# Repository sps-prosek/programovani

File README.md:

# Programování – 3. ročník (Mechatronika)

Podklady pro předmět **Programování** na SPŠ, elektrotechnické zaměření – obor Mechatronika
(26-41-M/01 Elektrotechnika, ŠVP Mechatronika, platnost od 1. 9. 2024).
Ve 3. ročníku se navazuje na základy jazyka C z 2. ročníku a programuje se mikrokontroler
na platformě **Arduino** (ATmega328P – UNO / Nano).

**Dotace podle ŠVP:** 2 h týdně, 64 h v ročníku. Plán počítá s **50 h náplně
(25 dvouhodinovek)**, zbytek je rezerva na odpadlé hodiny, testy a dokončení projektů.

## Kde co je

| Cesta | Obsah |
|---|---|
| `plan/` | ŠVP (`6_SVP_M_2024.pdf`), tematický plán, přehled vybavení, mapování starých podkladů na nová témata. |
| `temata/` | Vlastní učivo. Jedna složka = jeden tematický blok, uvnitř prezentace, hodiny, úlohy, kód, obrázky a Moodle. |
| `temata/00_sablony/` | Šablony: prezentace (Beamer), příprava na hodinu, zadání úlohy, podklady pro Moodle. |
| `spolecne/` | Věci sdílené napříč tématy – Beamer motiv SPŠ a preambule, loga školy, společné obrázky, ukázky kódu. |
| `nastroje/` | Pomocné skripty: založení struktury, nové téma, překlad prezentací, přesun archivu. |
| `_archiv/` | Staré podklady z předchozích let (`3EA/`, `vyuka/`). Zdroj, ze kterého se materiál postupně přenáší do `temata/`. |

## Tematické bloky

| # | Téma | Hodin |
|---|---|---:|
| 01 | HW platformy a vývojové prostředí | 4 |
| 02 | Digitální výstupy – LED a bzučák | 2 |
| 03 | Digitální vstupy – tlačítka, pull-up, zákmity | 4 |
| 04 | Časování bez `delay()` – `millis()` a časovače | 4 |
| 05 | Stavové automaty – cyklistická blikačka | 4 |
| 06 | Funkce a strukturování kódu | 2 |
| 07 | Analogové vstupy a PWM | 4 |
| 08 | Sériová linka (UART) | 2 |
| 09 | Pole a řetězce – parsování příkazů | 2 |
| 10 | Modelářské servo | 2 |
| 11 | DC motor a H-můstek | 2 |
| 12 | Přerušení a inkrementální enkodér | 4 |
| 13 | Sběrnice I2C a SPI, senzory | 4 |
| 14 | LCD displej | 2 |
| 15 | Vlastní knihovny a správa verzí | 2 |
| 16 | Závěrečný projekt | 6 |
| | **celkem** | **50** |

Rozvržení do období, mapování na výsledky vzdělávání a učivo ŠVP a kontrola pokrytí:
[`plan/tematicky_plan.md`](plan/tematicky_plan.md).

> Názvy složek zůstávají z první verze struktury (`01_uvod_arduino`, `09_pole_a_retezce`, …),
> i když se názvy témat upřesnily podle ŠVP. Číslování odpovídá plánu i oddílům v Moodle.

## Průřezové prvky

V každé praktické hodině: zapojení podle schématu, ověření zapojení měřením
(multimetr / osciloskop) a commit hotové úlohy do vlastního repozitáře.

## Jak přidat nové téma

```powershell
.\nastroje\nove_tema.ps1 -Cislo 17 -Slug nazev_tematu -Nazev "Název tématu"
```

Skript vytvoří složku s kompletní strukturou a předplněnými šablonami.

## Jak přeložit prezentaci

```powershell
.\nastroje\build_prezentace.ps1 temata\03_digitalni_vstupy\prezentace\prezentace.tex
```

Vyžaduje TeX Live nebo MiKTeX s `latexmk` a XeLaTeX. PDF zůstane vedle zdroje
pod názvem podle tématu – `PRG-03_digitalni_vstupy.pdf` – aby šlo rozeznat
i po nahrání do Moodle. Vzhled (logo školy, barvy, sazba kódu v C/Arduino)
řeší `spolecne/styl/` – viz [`spolecne/styl/README.md`](spolecne/styl/README.md).

## Konvence

- Názvy složek a souborů: **malými písmeny, bez diakritiky, podtržítka** místo mezer (kvůli Gitu, LaTeXu a Arduino IDE).
- Arduino skica musí být ve složce se stejným názvem jako soubor `.ino`.
- Prezentace, zadání i přípravy patří vždy do složky svého tématu, ne do sdíleného „koše“.
- Vygenerovaná PDF se do Gitu commitují (hodí se mít je po ruce), pomocné soubory LaTeXu ne – viz `.gitignore`.

## Kontakt

Jaroslav Bušek
[jaroslav.busek@sps-prosek.cz](mailto:jaroslav.busek@sps-prosek.cz)

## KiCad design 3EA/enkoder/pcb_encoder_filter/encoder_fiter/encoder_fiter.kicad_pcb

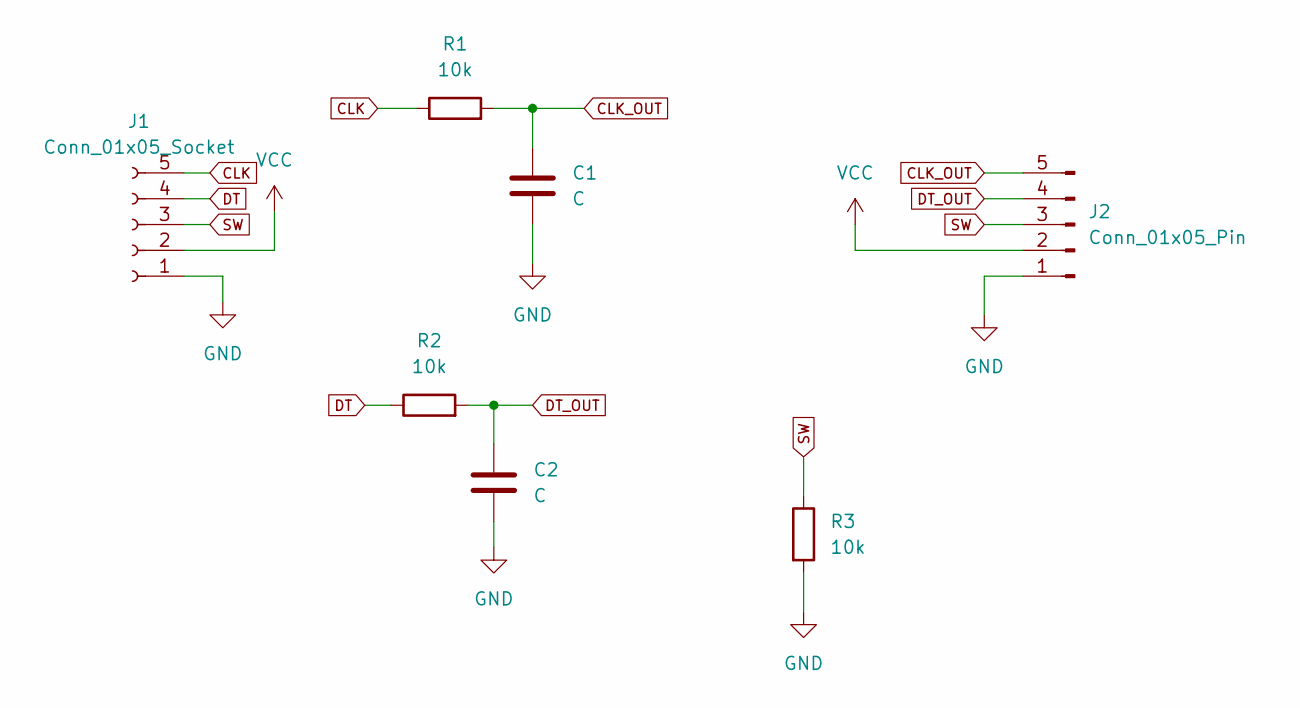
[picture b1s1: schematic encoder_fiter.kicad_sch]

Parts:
C1, C2: C; C_0805_2012Metric_Pad1.18x1.45mm_HandSolder
J1: Conn_01x05_Socket; PinSocket_1x05_P2.54mm_Horizontal
J2: Conn_01x05_Pin; PinHeader_1x05_P2.54mm_Horizontal
R1, R2, R3: 10k; C_0805_2012Metric_Pad1.18x1.45mm_HandSolder

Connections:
CLK: J1.5, R1.1
CLK_OUT: C1.1, J2.5, R1.2
DT: J1.4, R2.1
DT_OUT: C2.1, J2.4, R2.2
GND: C1.2, C2.2, J1.1, J2.1, R3.2
SW: J1.3, J2.3, R3.1
VCC: J1.2, J2.2

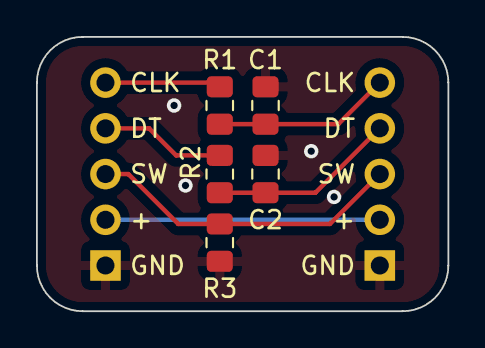
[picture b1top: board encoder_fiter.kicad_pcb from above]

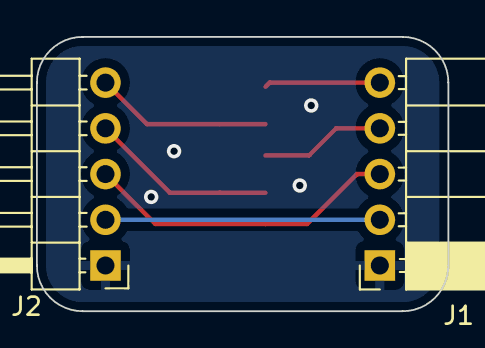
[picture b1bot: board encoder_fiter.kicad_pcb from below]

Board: 2 copper layers, 22.9 x 15.2 mm, 7 parts (2 on the bottom side), 7 nets.

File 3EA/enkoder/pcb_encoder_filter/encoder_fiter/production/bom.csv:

Designator,Footprint,Quantity,Value,LCSC Part #
"C1, C2",0805,2,C,
J1,PinSocket_1x05_P2.54mm_Horizontal,1,Conn_01x05_Socket,
J2,PinHeader_1x05_P2.54mm_Horizontal,1,Conn_01x05_Pin,
"R1, R2, R3",0805,3,10k,

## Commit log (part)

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2023-03-03 Update lcd_displej_s_tlacitkem.ino
    added row
2023-03-03 Update lcd_displej_s_tlacitkem.ino
    removed line
2023-03-03 Update lcd_displej_s_tlacitkem.ino
    removed comment obnov_displej()
2023-03-03 Update lcd_displej_s_tlacitkem_pomoci_funkci.ino
    missing ;
2023-09-15 Update init.ino
    pokusná změna pro 3EA
2024-03-07 PCB pro enkoder
2024-05-10 motor
